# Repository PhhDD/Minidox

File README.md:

# Minidox
My first keyboard pcb

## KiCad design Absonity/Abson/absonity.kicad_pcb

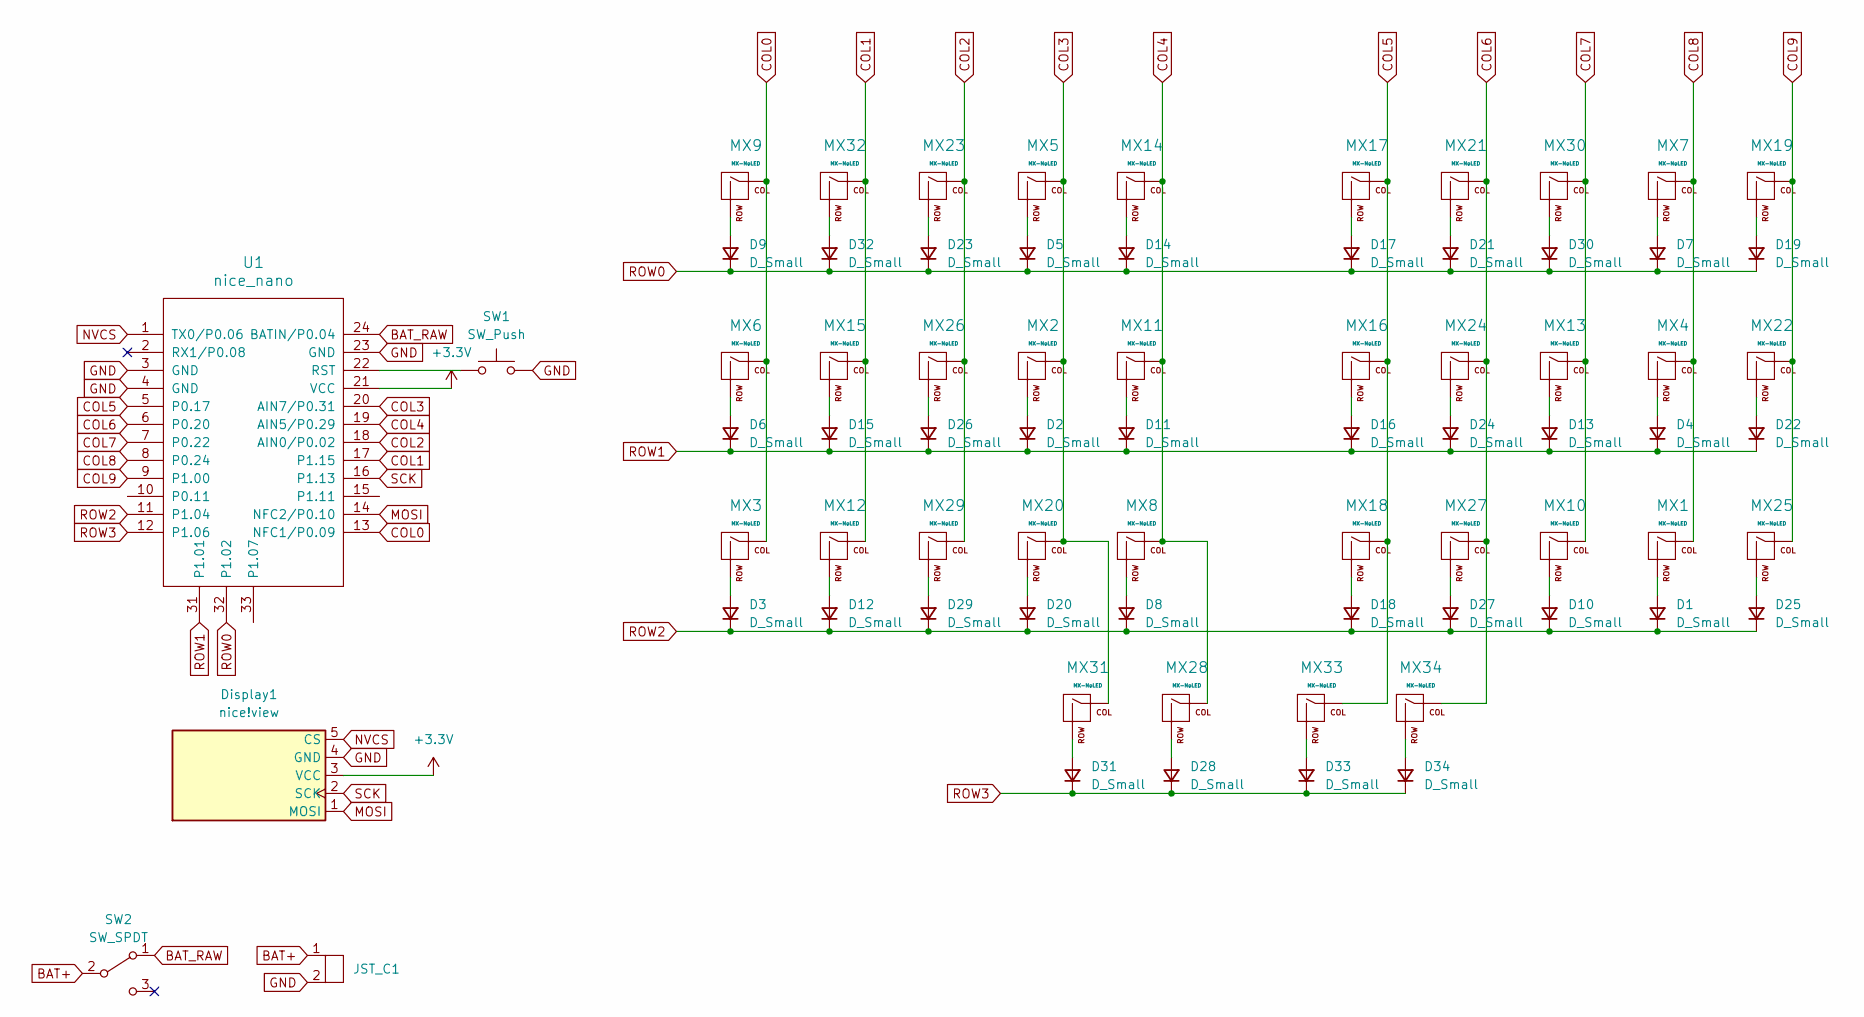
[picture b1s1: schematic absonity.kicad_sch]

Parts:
D1, D2, D3, D4, D5, D6, D7, D8, D9, D10, D11, D12, D13, D14, D15, D16, D17, D18, D19, D20, D21, D22, D23, D24, D25, D26, D27, D28, D29, D30, D31, D32, D33, D34: D_Small; D_SOD-123
Display1: nice!view; nice_view
JST_C1: JST_PH_S2B-PH-K_1x02_P2.00mm_Horizontal
MX1, MX2, MX3, MX4, MX5, MX6, MX7, MX8, MX9, MX10, MX11, MX12, MX13, MX14, MX15, MX16, MX17, MX18, MX19, MX20, MX21, MX22, MX23, MX24, MX25, MX26, MX27, MX29, MX30, MX31, MX32, MX34: MX-NoLED; MXOnly-1U-Hotswap
MX28, MX33: MX-NoLED; MXOnly-1.5U-Hotswap
SW1: SW_Push; SW_RESET
SW2: SW_SPDT; SW_SPDT_PCM12
U1: nice_nano

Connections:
+3.3V: Display1.3 (VCC), U1.21 (VCC)
BAT+: JST_C1.1, SW2.2 (B)
BAT_RAW: SW2.1 (A), U1.24 (BATIN/P0.04)
COL0: MX3.1 (COL), MX6.1 (COL), MX9.1 (COL), U1.13 (NFC1/P0.09)
COL1: MX12.1 (COL), MX15.1 (COL), MX32.1 (COL), U1.17 (P1.15)
COL2: MX23.1 (COL), MX26.1 (COL), MX29.1 (COL), U1.18 (AIN0/P0.02)
COL3: MX2.1 (COL), MX5.1 (COL), MX20.1 (COL), MX31.1 (COL), U1.20 (AIN7/P0.31)
COL4: MX8.1 (COL), MX11.1 (COL), MX14.1 (COL), MX28.1 (COL), U1.19 (AIN5/P0.29)
COL5: MX16.1 (COL), MX17.1 (COL), MX18.1 (COL), MX33.1 (COL), U1.5 (P0.17)
COL6: MX21.1 (COL), MX24.1 (COL), MX27.1 (COL), MX34.1 (COL), U1.6 (P0.20)
COL7: MX10.1 (COL), MX13.1 (COL), MX30.1 (COL), U1.7 (P0.22)
COL8: MX1.1 (COL), MX4.1 (COL), MX7.1 (COL), U1.8 (P0.24)
COL9: MX19.1 (COL), MX22.1 (COL), MX25.1 (COL), U1.9 (P1.00)
GND: Display1.4 (GND), JST_C1.2, SW1.2, U1.3 (GND), U1.4 (GND), U1.23 (GND)
MOSI: Display1.1 (MOSI), U1.14 (NFC2/P0.10)
NVCS: Display1.5 (CS), U1.1 (TX0/P0.06)
unnamed: D1.2 (A), MX1.2 (ROW)
unnamed: D2.2 (A), MX2.2 (ROW)
unnamed: D3.2 (A), MX3.2 (ROW)
unnamed: D4.2 (A), MX4.2 (ROW)
unnamed: D5.2 (A), MX5.2 (ROW)
unnamed: D6.2 (A), MX6.2 (ROW)
unnamed: D7.2 (A), MX7.2 (ROW)
unnamed: D8.2 (A), MX8.2 (ROW)
unnamed: D9.2 (A), MX9.2 (ROW)
unnamed: D10.2 (A), MX10.2 (ROW)
unnamed: D11.2 (A), MX11.2 (ROW)
unnamed: D12.2 (A), MX12.2 (ROW)
unnamed: D13.2 (A), MX13.2 (ROW)
unnamed: D14.2 (A), MX14.2 (ROW)
unnamed: D15.2 (A), MX15.2 (ROW)
unnamed: D16.2 (A), MX16.2 (ROW)
unnamed: D17.2 (A), MX17.2 (ROW)
unnamed: D18.2 (A), MX18.2 (ROW)
unnamed: D19.2 (A), MX19.2 (ROW)
unnamed: D20.2 (A), MX20.2 (ROW)
unnamed: D21.2 (A), MX21.2 (ROW)
unnamed: D22.2 (A), MX22.2 (ROW)
unnamed: D23.2 (A), MX23.2 (ROW)
unnamed: D24.2 (A), MX24.2 (ROW)
unnamed: D25.2 (A), MX25.2 (ROW)
unnamed: D26.2 (A), MX26.2 (ROW)
unnamed: D27.2 (A), MX27.2 (ROW)
unnamed: D28.2 (A), MX28.2 (ROW)
unnamed: D29.2 (A), MX29.2 (ROW)
unnamed: D30.2 (A), MX30.2 (ROW)
unnamed: D31.2 (A), MX31.2 (ROW)
unnamed: D32.2 (A), MX32.2 (ROW)
unnamed: D33.2 (A), MX33.2 (ROW)
unnamed: D34.2 (A), MX34.2 (ROW)
unnamed: SW1.1, U1.22 (RST)
ROW0: D5.1 (K), D7.1 (K), D9.1 (K), D14.1 (K), D17.1 (K), D19.1 (K), D21.1 (K), D23.1 (K), D30.1 (K), D32.1 (K), U1.32 (P1.02)
ROW1: D2.1 (K), D4.1 (K), D6.1 (K), D11.1 (K), D13.1 (K), D15.1 (K), D16.1 (K), D22.1 (K), D24.1 (K), D26.1 (K), U1.31 (P1.01)
ROW2: D1.1 (K), D3.1 (K), D8.1 (K), D10.1 (K), D12.1 (K), D18.1 (K), D20.1 (K), D25.1 (K), D27.1 (K), D29.1 (K), U1.11 (P1.04)
ROW3: D28.1 (K), D31.1 (K), D33.1 (K), D34.1 (K), U1.12 (P1.06)
SCK: Display1.2 (SCK), U1.16 (P1.13)

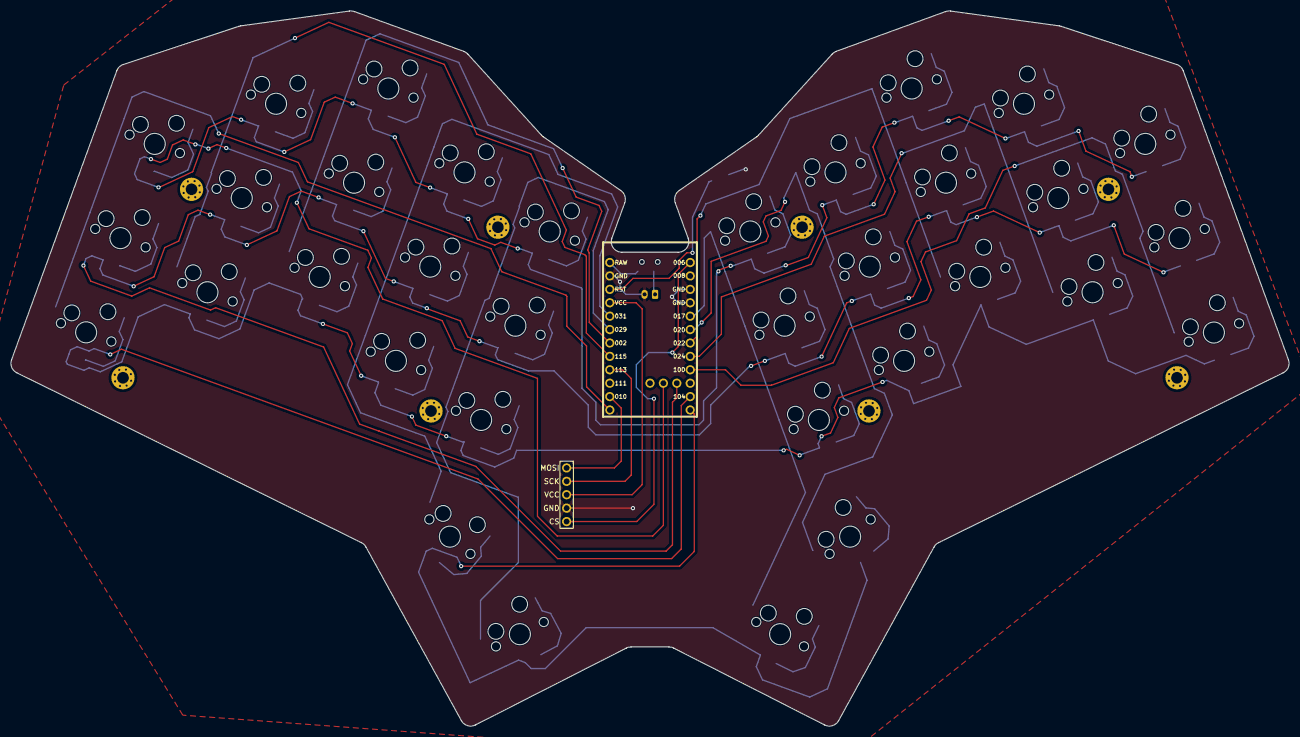
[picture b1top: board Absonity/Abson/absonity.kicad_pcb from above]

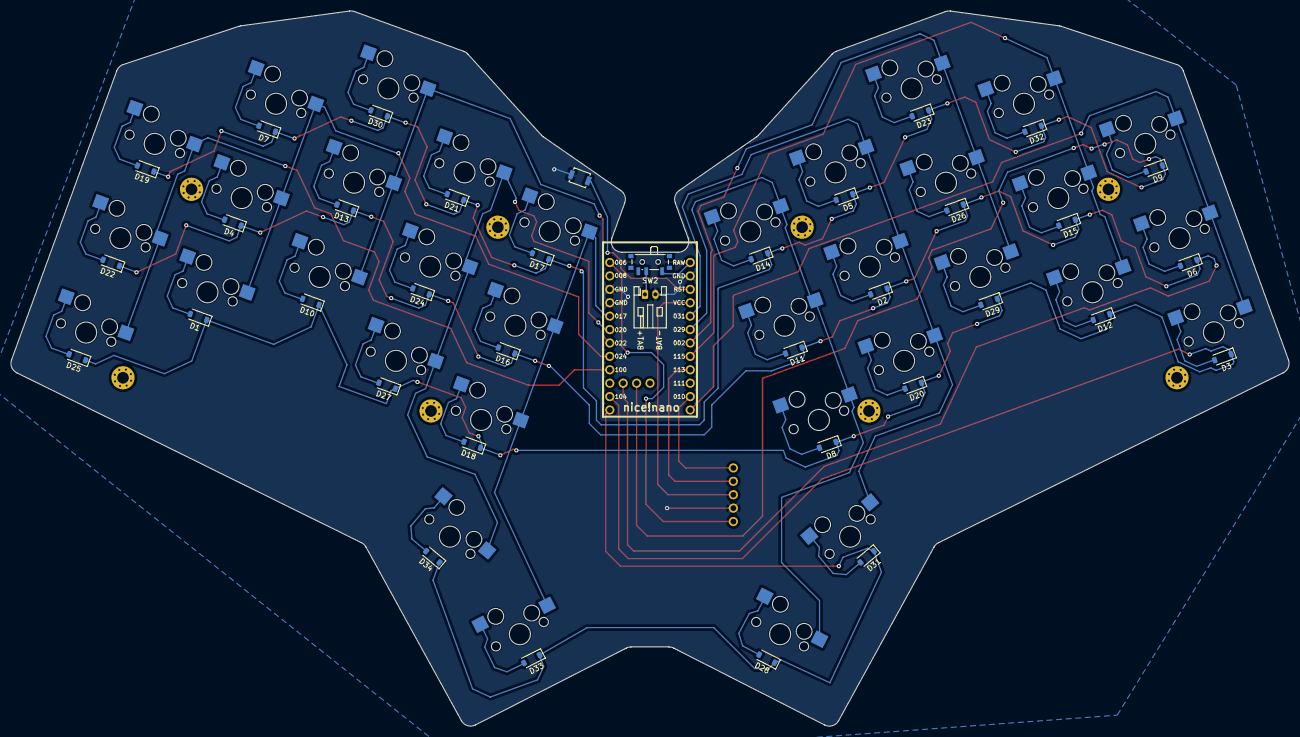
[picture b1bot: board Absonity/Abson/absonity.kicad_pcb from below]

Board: 2 copper layers, 242.2 x 135.5 mm, 81 parts (38 on the bottom side), 56 nets.

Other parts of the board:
_1, _2, _3, _4, _5, _6, _7, _8: MountingHole_2.2mm_M2_Pad_Via

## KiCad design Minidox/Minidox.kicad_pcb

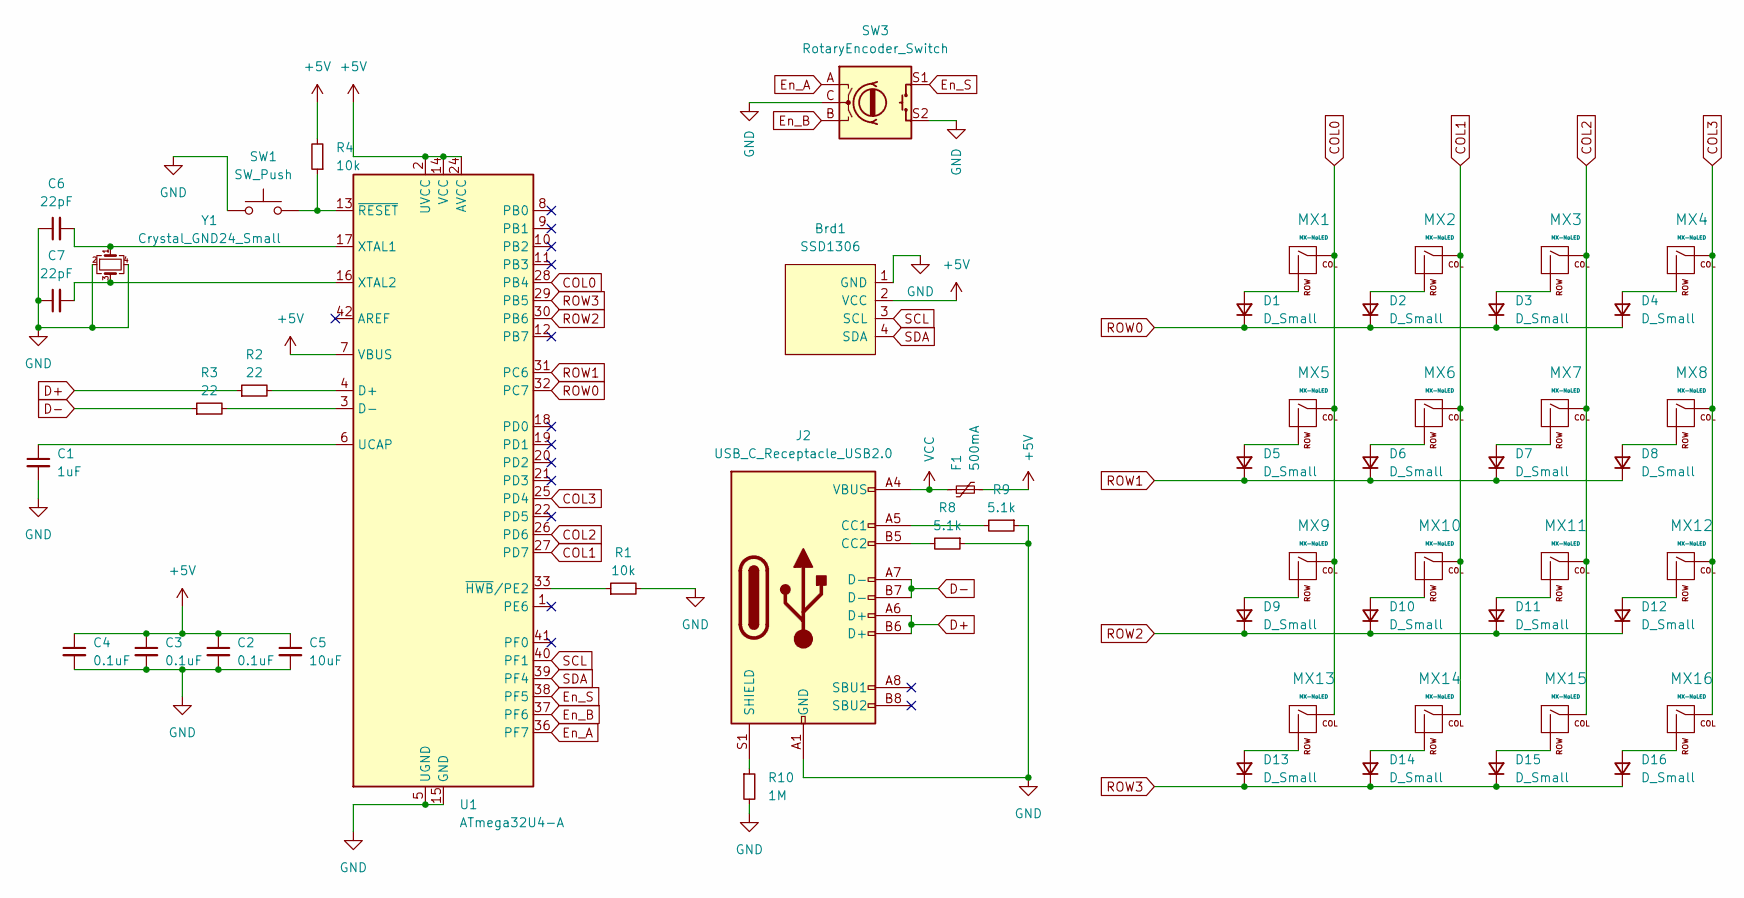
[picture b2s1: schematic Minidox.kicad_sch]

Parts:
Brd1: SSD1306; 128x64OLED
C1: 1uF; C_0805_2012Metric_Pad1.18x1.45mm_HandSolder
C2, C3, C4: 0.1uF; C_0805_2012Metric_Pad1.18x1.45mm_HandSolder
C5: 10uF; C_0805_2012Metric_Pad1.18x1.45mm_HandSolder
C6, C7: 22pF; C_0805_2012Metric_Pad1.18x1.45mm_HandSolder
D1, D2, D3, D4, D5, D6, D7, D8, D9, D10, D11, D12, D13, D14, D15, D16: D_Small; D_SOD-123
F1: 500mA; Fuse_1206_3216Metric_Pad1.42x1.75mm_HandSolder
J2: USB_C_Receptacle_USB2.0; USB_C_Receptacle_HRO_TYPE-C-31-M-12
MX1, MX2, MX3, MX4, MX5, MX6, MX7, MX8, MX9, MX10, MX11, MX12, MX13, MX14, MX15, MX16: MX-NoLED; MX-1U-NoLED
R1, R4: 10k; R_0805_2012Metric_Pad1.20x1.40mm_HandSolder
R2, R3: 22; R_0805_2012Metric_Pad1.20x1.40mm_HandSolder
R8, R9: 5.1k; R_0805_2012Metric_Pad1.20x1.40mm_HandSolder
R10: 1M; R_0805_2012Metric_Pad1.20x1.40mm_HandSolder
SW1: SW_Push; SKQG-1155865
SW3: RotaryEncoder_Switch; RotaryEncoder_Alps_EC11E-Switch_Vertical_H20mm_CircularMoun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
U1: ATmega32U4-A; TQFP-44_10x10mm_P0.8mm
Y1: Crystal_GND24_Small; Crystal_SMD_3225-4Pin_3.2x2.5mm_HandSoldering

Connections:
+5V: Brd1.2 (VCC), C2.1, C3.1, C4.1, C5.1, F1.2, R4.2, U1.2 (UVCC), U1.7 (VBUS), U1.14 (VCC), U1.24 (AVCC), U1.34 (VCC), U1.44 (AVCC)
COL0: MX1.1 (COL), MX5.1 (COL), MX9.1 (COL), MX13.1 (COL), U1.28 (PB4)
COL1: MX2.1 (COL), MX6.1 (COL), MX10.1 (COL), MX14.1 (COL), U1.27 (PD7)
COL2: MX3.1 (COL), MX7.1 (COL), MX11.1 (COL), MX15.1 (COL), U1.26 (PD6)
COL3: MX4.1 (COL), MX8.1 (COL), MX12.1 (COL), MX16.1 (COL), U1.25 (PD4)
D+: J2.A6 (D+), J2.B6 (D+), R2.1
D-: J2.A7 (D-), J2.B7 (D-), R3.1
En_A: SW3.A, U1.36 (PF7)
En_B: SW3.B, U1.37 (PF6)
En_S: SW3.S1, U1.38 (PF5)
GND: Brd1.1 (GND), C1.2, C2.2, C3.2, C4.2, C5.2, C6.1, C7.1, J2.A1 (GND), J2.A12 (GND), J2.B1 (GND), J2.B12 (GND), R1.2, R8.1, R9.1, R10.2, SW1.1, SW3.C, SW3.S2, U1.5 (UGND), U1.15 (GND), U1.23 (GND), U1.35 (GND), U1.43 (GND), Y1.2, Y1.4
unnamed: D1.2 (A), MX1.2 (ROW)
unnamed: D2.2 (A), MX2.2 (ROW)
unnamed: D3.2 (A), MX3.2 (ROW)
unnamed: D4.2 (A), MX4.2 (ROW)
unnamed: D5.2 (A), MX5.2 (ROW)
unnamed: D6.2 (A), MX6.2 (ROW)
unnamed: D7.2 (A), MX7.2 (ROW)
unnamed: D8.2 (A), MX8.2 (ROW)
unnamed: D9.2 (A), MX9.2 (ROW)
unnamed: D10.2 (A), MX10.2 (ROW)
unnamed: D11.2 (A), MX11.2 (ROW)
unnamed: D12.2 (A), MX12.2 (ROW)
unnamed: D13.2 (A), MX13.2 (ROW)
unnamed: D14.2 (A), MX14.2 (ROW)
unnamed: D15.2 (A), MX15.2 (ROW)
unnamed: D16.2 (A), MX16.2 (ROW)
unnamed: J2.A5 (CC1), R9.2
unnamed: J2.B5 (CC2), R8.2
unnamed: J2.S1 (SHIELD), R10.1
unnamed: R2.2, U1.4 (D+)
unnamed: R3.2, U1.3 (D-)
unnamed: C1.1, U1.6 (UCAP)
unnamed: C6.2, U1.17 (XTAL1), Y1.1
unnamed: C7.2, U1.16 (XTAL2), Y1.3
unnamed: R1.1, U1.33 (~HWB/PE2)
unnamed: R4.1, SW1.2, U1.13 (~RESET)
ROW0: D1.1 (K), D2.1 (K), D3.1 (K), D4.1 (K), U1.32 (PC7)
ROW1: D5.1 (K), D6.1 (K), D7.1 (K), D8.1 (K), U1.31 (PC6)
ROW2: D9.1 (K), D10.1 (K), D11.1 (K), D12.1 (K), U1.30 (PB6)
ROW3: D13.1 (K), D14.1 (K), D15.1 (K), D16.1 (K), U1.29 (PB5)
SCL: Brd1.3 (SCL), U1.40 (PF1)
SDA: Brd1.4 (SDA), U1.39 (PF4)
VCC: F1.1, J2.A4 (VBUS), J2.A9 (VBUS), J2.B4 (VBUS), J2.B9 (VBUS)

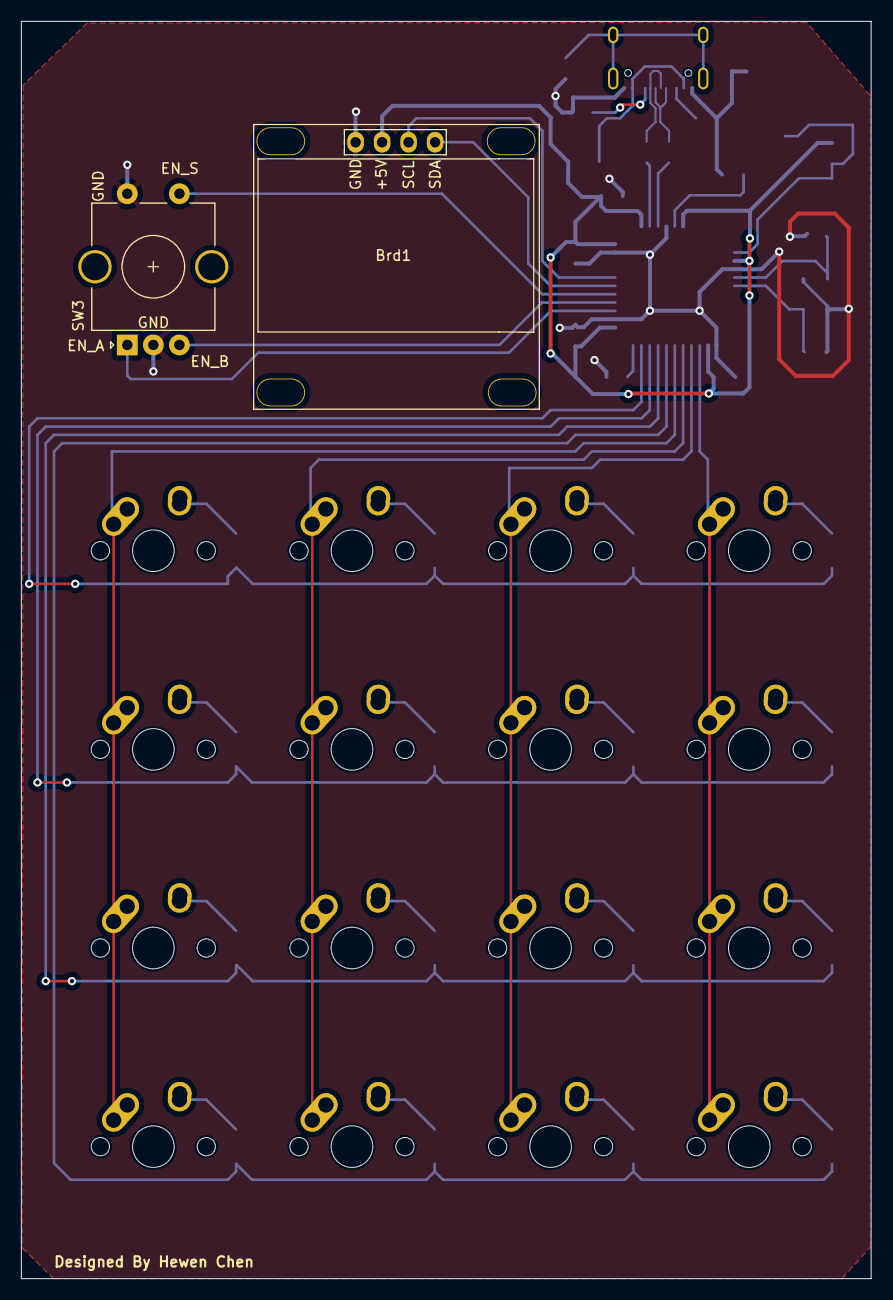
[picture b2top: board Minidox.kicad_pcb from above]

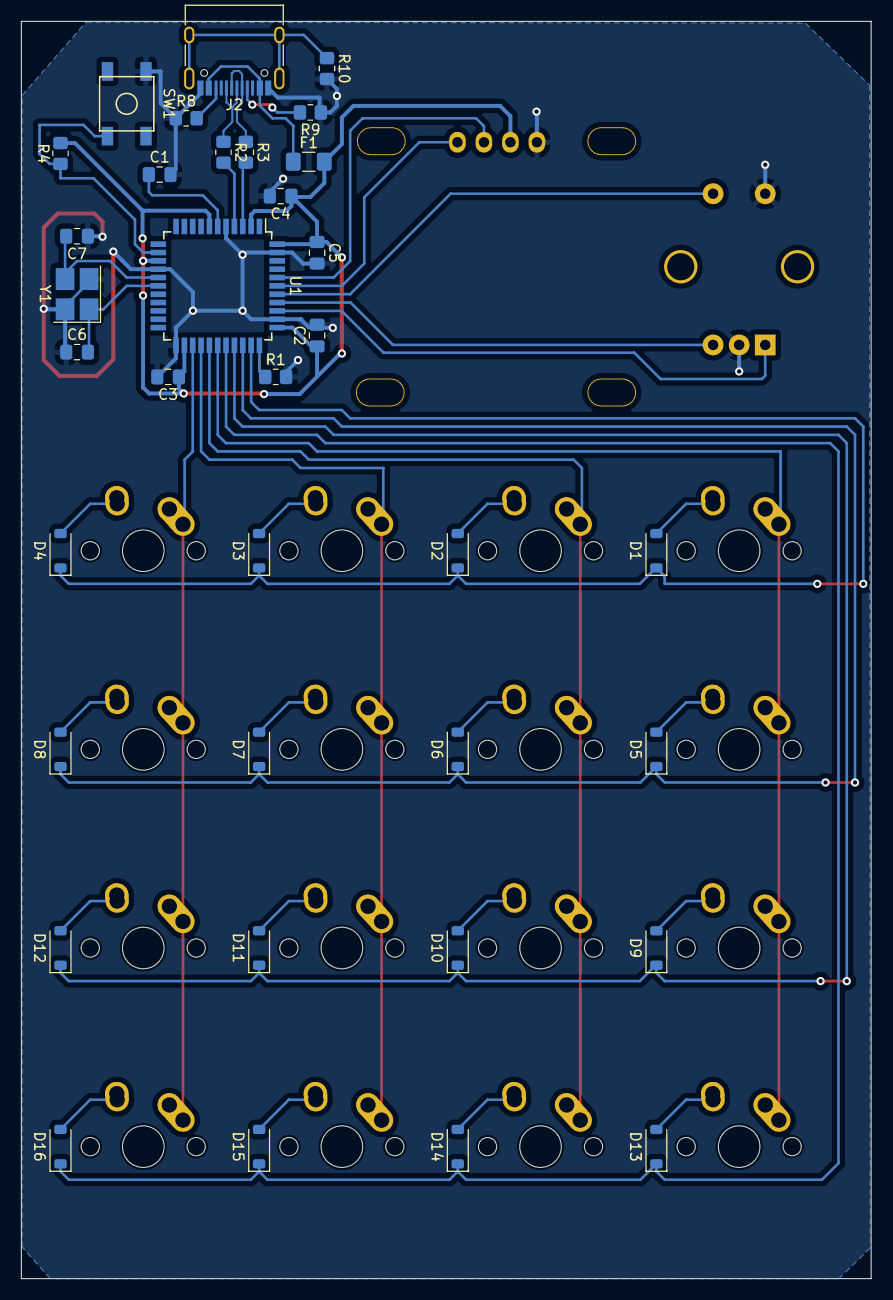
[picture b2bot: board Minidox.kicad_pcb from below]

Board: 2 copper layers, 81.5 x 120.6 mm, 53 parts (35 on the bottom side), 44 nets.

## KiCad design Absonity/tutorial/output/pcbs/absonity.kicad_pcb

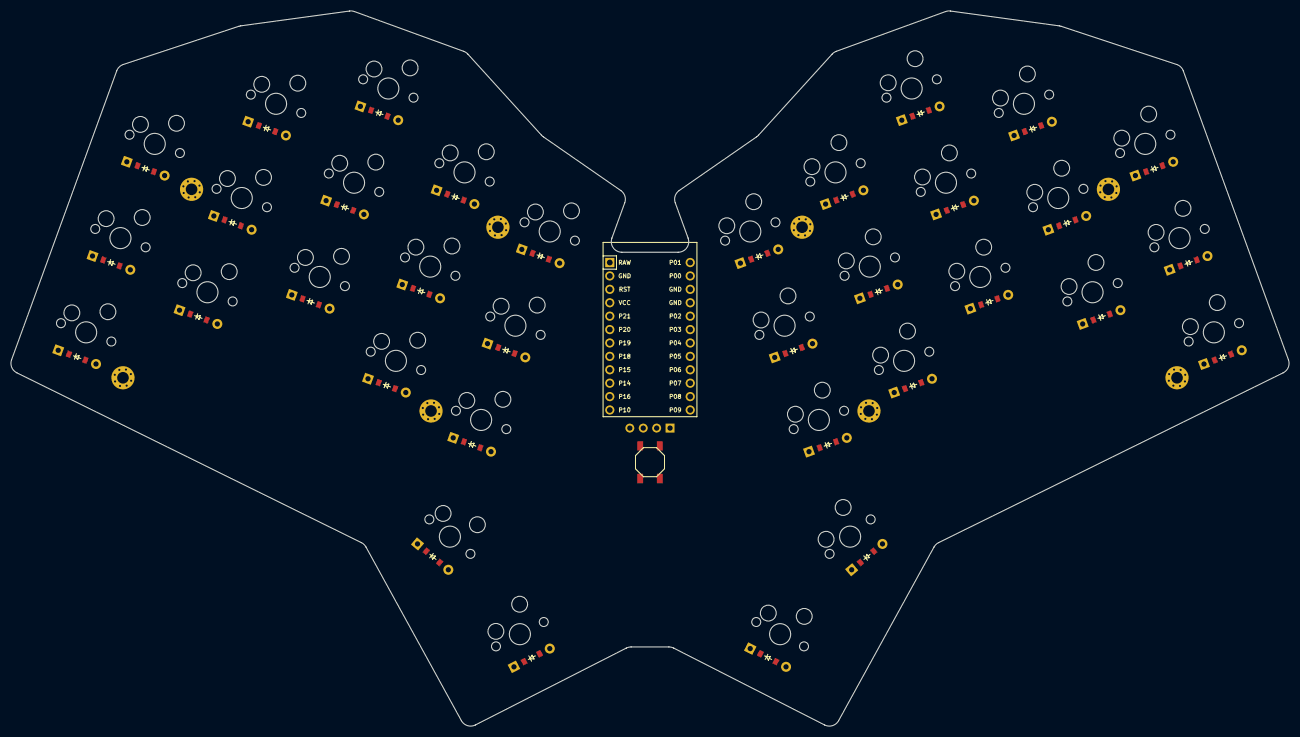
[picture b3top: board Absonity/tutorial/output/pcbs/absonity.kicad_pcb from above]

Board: 2 copper layers, 242.2 x 135.5 mm, 79 parts (0 on the bottom side), 50 nets, no tracks yet.

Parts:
B1: SW_TACT_ALPS_SKQGABE010
D1, D2, D3, D4, D5, D6, D7, D8, D9, D10, D11, D12, D13, D14, D15, D16, D17, D18, D19, D20, D21, D22, D23, D24, D25, D26, D27, D28, D29, D30, D31, D32, D33, D34: ComboDiode
MCU1: ProMicro
OLED1: OLED; OLED_headers
S1, S2, S3, S4, S5, S6, S7, S8, S9, S10, S11, S12, S13, S14, S15, S16, S17, S18, S19, S20, S21, S22, S23, S24, S25, S26, S27, S28, S29, S30, S31, S32, S33, S34: MX
_1, _2, _3, _4, _5, _6, _7, _8: MountingHole_2.2mm_M2_Pad_Via

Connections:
GND: B1.1, MCU1.2, MCU1.15, MCU1.16, OLED1.1
P1: MCU1.13, S18.1, S19.1, S20.1
P2: MCU1.17, OLED1.4
P3: MCU1.18, OLED1.3
P4: MCU1.19, S21.1, S22.1, S23.1
P5: MCU1.20, S24.1, S25.1, S26.1
P6: MCU1.21, S27.1, S28.1, S29.1
P7: MCU1.22, S30.1, S31.1, S32.1
P10: D1.1, D4.1, D7.1, D10.1, D13.1, D18.1, D21.1, D24.1, D27.1, D30.1, MCU1.12
P14: D3.1, D6.1, D9.1, D12.1, D15.1, D20.1, D23.1, D26.1, D29.1, D32.1, MCU1.10, S1.1, S2.1, S3.1
P16: D2.1, D5.1, D8.1, D11.1, D14.1, D19.1, D22.1, D25.1, D28.1, D31.1, MCU1.11
P18: MCU1.8, S13.1, S14.1, S15.1
P20: MCU1.6, S7.1, S8.1, S9.1
P21: MCU1.5, S4.1, S5.1, S6.1
RST: B1.2, MCU1.3
VCC: MCU1.4, OLED1.2
index_bottom: D14.2, S14.2
index_home: D15.2, S15.2
index_mods: D13.2, S13.2
layer_cluster: D16.2, S16.2
middle_bottom: D11.2, S11.2
middle_home: D12.2, S12.2
middle_mods: D10.2, S10.2
mirror_index_bottom: D31.2, S31.2
mirror_index_home: D32.2, S32.2
mirror_index_mods: D30.2, S30.2
mirror_layer_cluster: D33.2, S33.2
mirror_middle_bottom: D28.2, S28.2
mirror_middle_home: D29.2, S29.2
mirror_middle_mods: D27.2, S27.2
mirror_outer_bottom: D19.2, S19.2
mirror_outer_home: D20.2, S20.2
mirror_outer_mods: D18.2, S18.2
mirror_pinky_bottom: D22.2, S22.2
mirror_pinky_home: D23.2, S23.2
mirror_pinky_mods: D21.2, S21.2
mirror_ring_bottom: D25.2, S25.2
mirror_ring_home: D26.2, S26.2
mirror_ring_mods: D24.2, S24.2
mirror_space_cluster: D34.2, S34.2
outer_bottom: D2.2, S2.2
outer_home: D3.2, S3.2
outer_mods: D1.2, S1.2
pinky_bottom: D5.2, S5.2
pinky_home: D6.2, S6.2
pinky_mods: D4.2, S4.2
ring_bottom: D8.2, S8.2
ring_home: D9.2, S9.2
ring_mods: D7.2, S7.2
space_cluster: D17.2, S17.2

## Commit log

2023-07-17 Creation of the Files
2023-07-17 Added Parts
2023-07-18 Done
2023-07-28 Absonity
